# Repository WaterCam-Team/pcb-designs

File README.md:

# SU WaterCam PCB

Custom KiCad HAT for the **SU-WaterCam** project. Stacks on a Raspberry Pi 4B via a WittyPi 4 RTC/power-manager board, adding thermal imaging, LoRaWAN telemetry, IMU orientation, and environmental sensing.

**Software repo:** [mandeeps/SU-WaterCam](https://github.com/mandeeps/SU-WaterCam)  
**Schematic/pin map:** [PIN_MAP.md](PIN_MAP.md)

---

## Stack Order

Raspberry Pi 4B → WittyPi 4 (stacking header) → WaterCam HAT

---

## Components

| Reference | Part | Interface | Notes |
|-----------|------|-----------|-------|
| U2 | Adafruit BNO055 STEMMA QT | I2C1 (0x28) | 9-DOF IMU; INT→GPIO20, RST→GPIO16 |
| U3 | Multitech MTDOT-915 | UART5 (GPIO12/13) | LoRaWAN; always-on 3.3 V from WittyPi J3 |
| U1 | Adafruit AHT20 | I2C1 (0x38) | Temp/humidity |
| J2 | FLIR Lepton Breakout v2 | SPI0 + I2C1 | 2×10 header; SPI for image data, I2C for CCI |
| J3 | WittyPi 4 P3 header | — | Taps always-on 3.3 V and SW pin for mDot |
| Q1 | MOSFET | — | mDot PB_1 pulls WittyPi SW low for remote wake |

---

## Power Domains

| Rail | Source | Powers |
|------|--------|--------|
| +3V3 (Pi) | Pi J1 pin 1 | AHT20, BNO055 breakout, I2C pull-ups R6/R7 |
| 5 V (Pi) | Pi J1 pin 2/4 | FLIR Lepton VIN (J2-P2) |
| 3.3 V (always-on) | WittyPi J3 pin 2 | mDot VDD, mDot NRESET pull-up — survives Pi shutdown |

---

## PCB Details

- **Layers:** 2 (F.Cu, B.Cu)
- **Signal traces:** 0.25 mm
- **Power traces:** 0.5 mm
- **Clearance:** 0.20 mm (default net class)

---

## PCB Images

- **Wiring/Layout Diagram**  

- **PCB Render**

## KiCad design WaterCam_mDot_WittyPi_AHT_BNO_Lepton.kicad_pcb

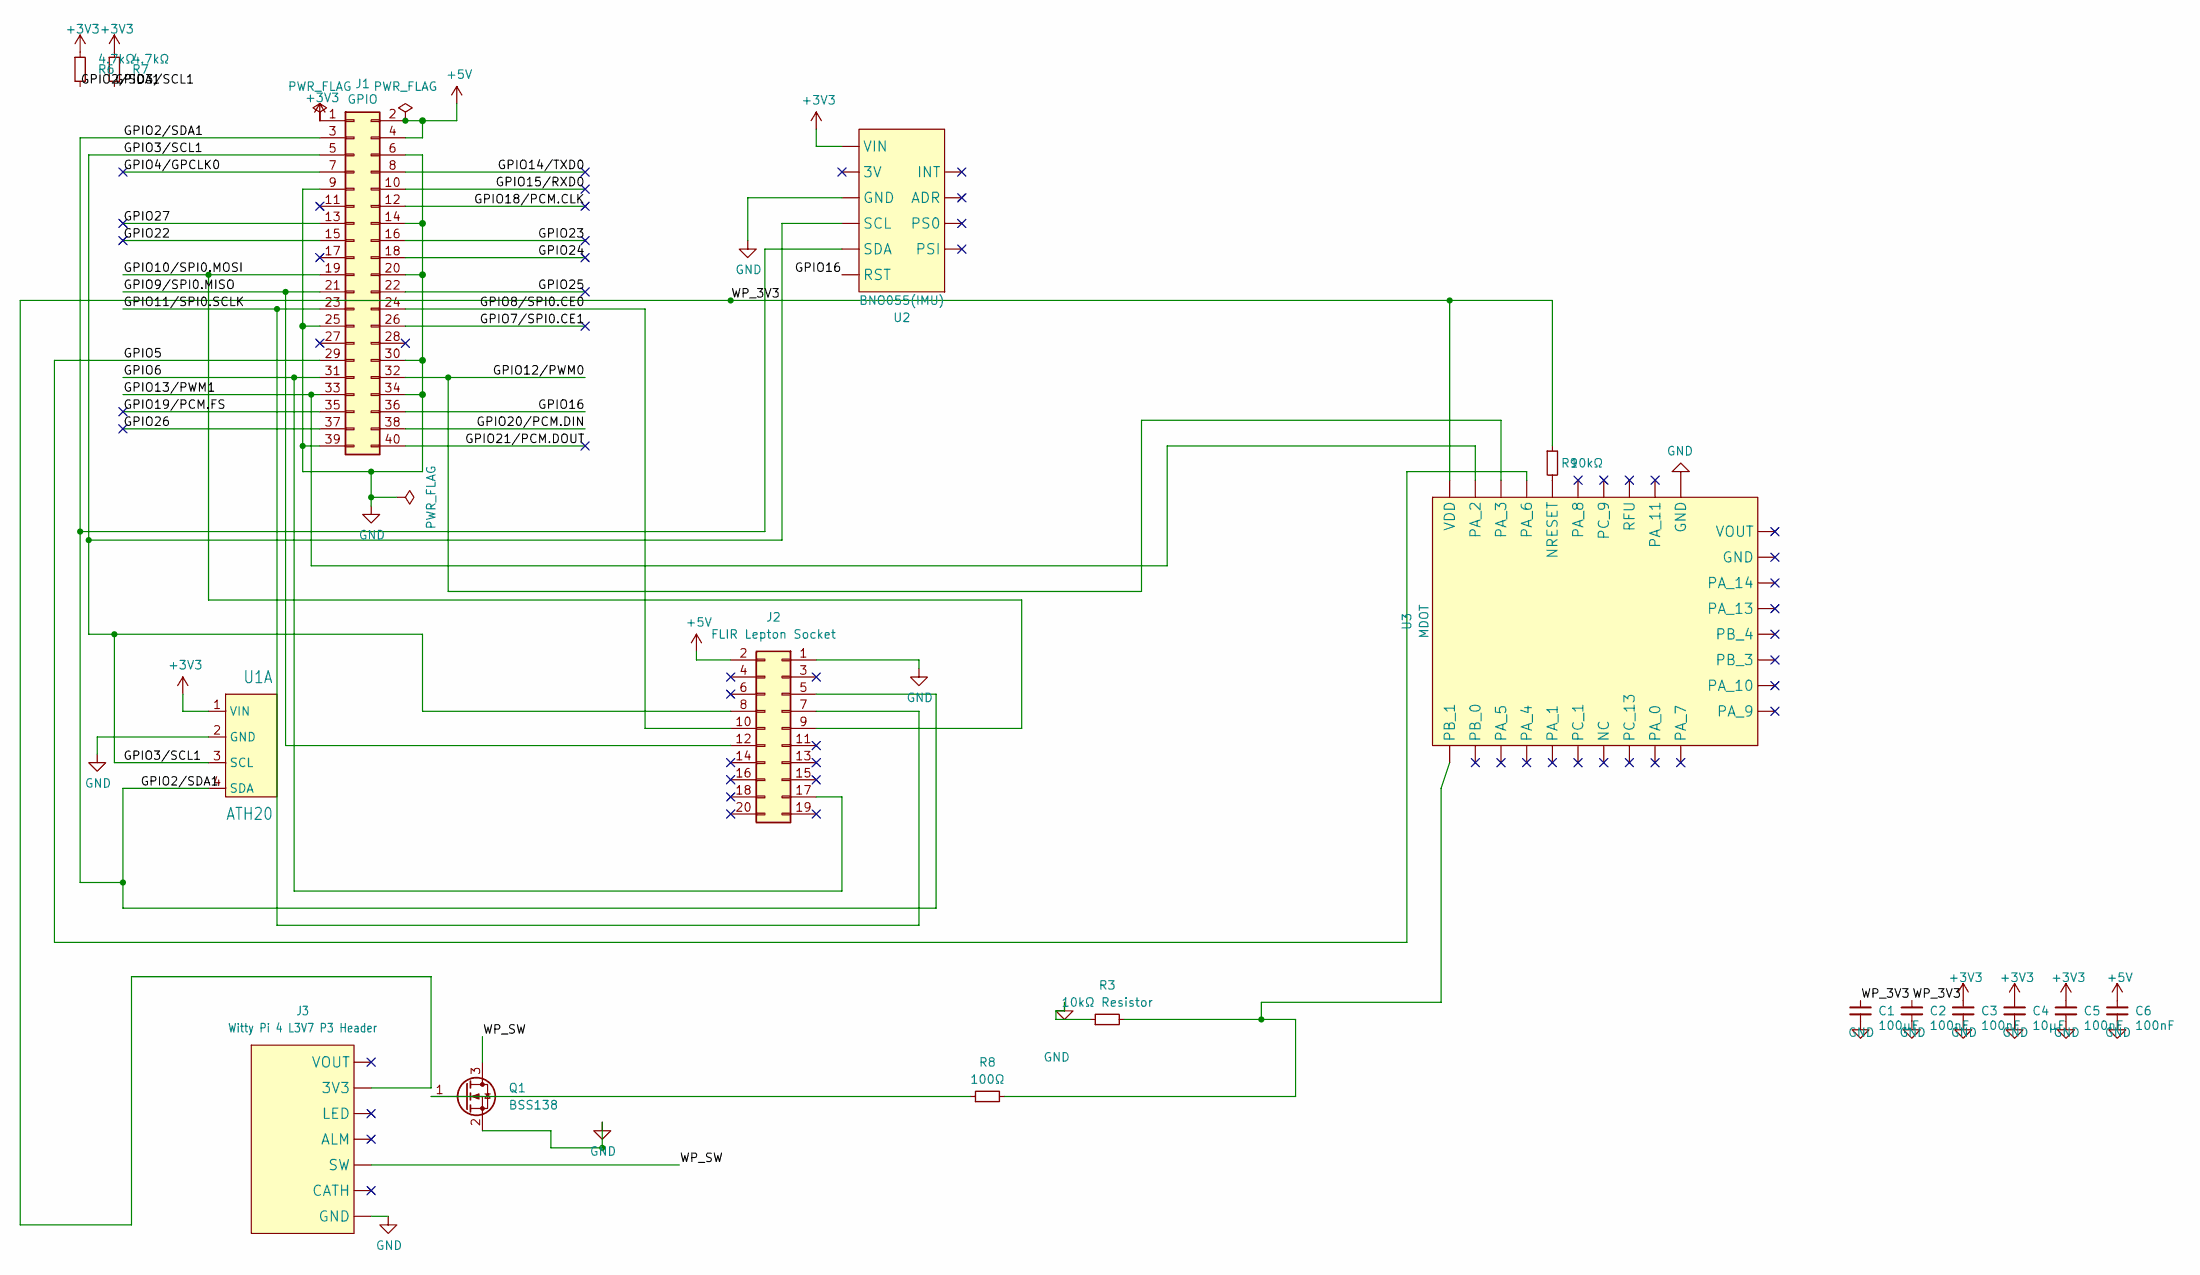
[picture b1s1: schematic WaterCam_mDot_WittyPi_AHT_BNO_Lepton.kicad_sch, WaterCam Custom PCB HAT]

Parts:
C1: 100µF; C_0805_2012Metric
C2, C3, C5, C6: 100nF; C_0402_1005Metric
C4: 10µF; C_0402_1005Metric
J1: GPIO; MODULE_RASPBERRY_PI_4B_4GB
J2: FLIR Lepton Socket; FLIR Lepton Breakout Board (Vertical)
J3: Witty Pi 4 L3V7 P3 Header; WittyPi4_Simple
Q1: BSS138; SOT-23
R3: 10kΩ Resistor; R_Axial_DIN0207_L6.3mm_D2.5mm_P2.54mm_Vertical
R6, R7: 4.7kΩ; R_0402_1005Metric
R8: 100Ω; R_0402_1005Metric
R9: 10kΩ; R_0402_1005Metric
U1: ATH20; AHT20 Breakout Board
U2: BNO055(IMU); BNO-055 Breakout
U3: MDOT; MTDOT

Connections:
+3V3: C3.1, C4.1, C5.1, J1.1, R6.1, R7.1, U1.1 (VIN), U2.6 (VIN)
+5V: C6.1, J1.2, J1.4, J2.2
/GPIO2/SDA1: J1.3, J2.5, R6.2, U1.4 (SDA), U2.2 (SDA)
/GPIO3/SCL1: J1.5, J2.8, R7.2, U1.3 (SCL), U2.3 (SCL)
/GPIO4/GPCLK0: J1.7
/GPIO5: J1.29, U3.4 (PA_6)
/GPIO6: J1.31, J2.17
/GPIO7/SPI0.CE1: J1.26
/GPIO8/SPI0.CE0: J1.24, J2.10
/GPIO9/SPI0.MISO: J1.21, J2.12
/GPIO10/SPI0.MOSI: J1.19, J2.9
/GPIO11/SPI0.SCLK: J1.23, J2.7
/GPIO12/PWM0: J1.32, U3.3 (PA_3)
/GPIO13/PWM1: J1.33, U3.2 (PA_2)
/GPIO14/TXD0: J1.8
/GPIO15/RXD0: J1.10
/GPIO16: J1.36, U2.1 (RST)
/GPIO18/PCM.CLK: J1.12
/GPIO19/PCM.FS: J1.35
/GPIO20/PCM.DIN: J1.38
/GPIO21/PCM.DOUT: J1.40
/GPIO22: J1.15
/GPIO23: J1.16
/GPIO24: J1.18
/GPIO25: J1.22
/GPIO26: J1.37
/GPIO27: J1.13
/WP_3V3: C1.1, C2.1, J3.2 (3V3), R9.1, U3.1 (VDD)
/WP_SW: J3.5 (SW), Q1.3 (D)
GND: C1.2, C2.2, C3.2, C4.2, C5.2, C6.2, J1.6, J1.9, J1.14, J1.20, J1.25, J1.30, J1.34, J1.39, J2.1, J3.7 (GND), Q1.2 (S), R3.1, U1.2 (GND), U2.4 (GND), U3.10 (GND)
unnamed: Q1.1 (G), R8.1
unnamed: R9.2, U3.5 (NRESET)
unnamed: R3.2, R8.2, U3.19 (PB_1)

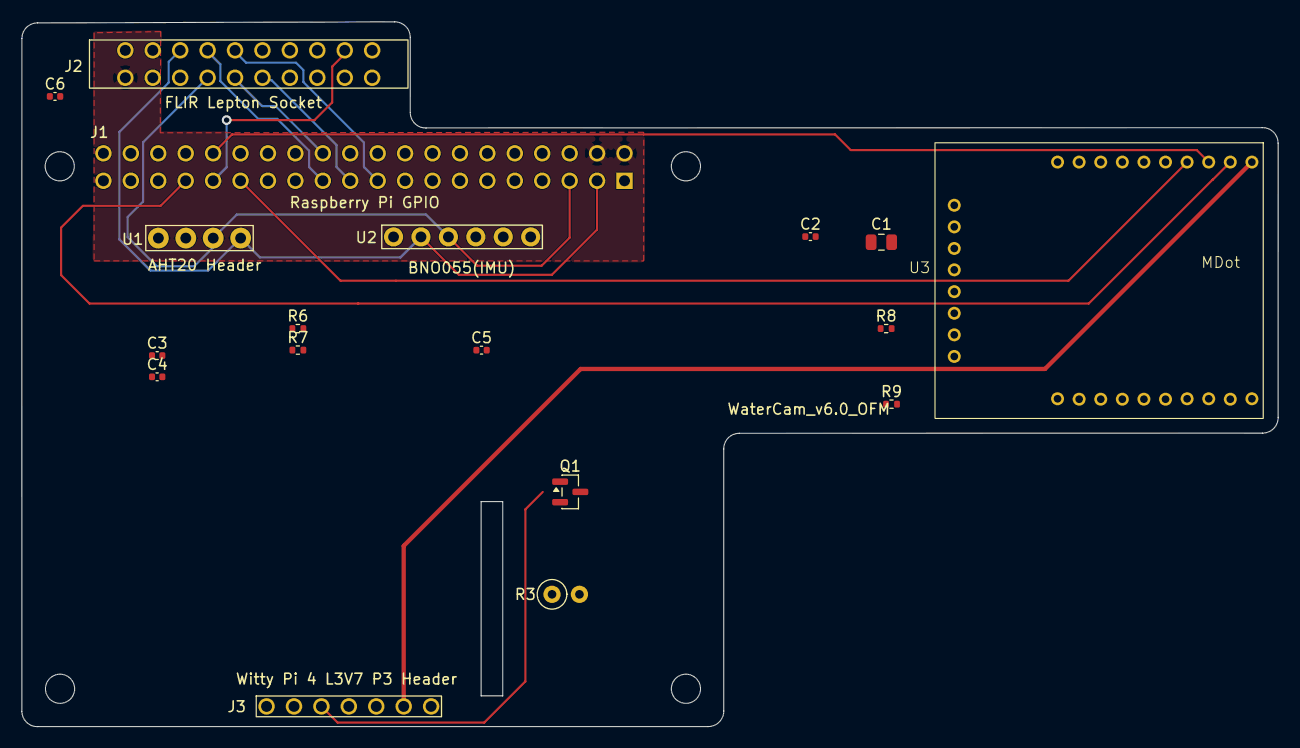
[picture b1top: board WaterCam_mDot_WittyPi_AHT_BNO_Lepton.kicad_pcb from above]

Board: 2 copper layers, 116.3 x 65.3 mm, 18 parts (1 on the bottom side), 19 nets.

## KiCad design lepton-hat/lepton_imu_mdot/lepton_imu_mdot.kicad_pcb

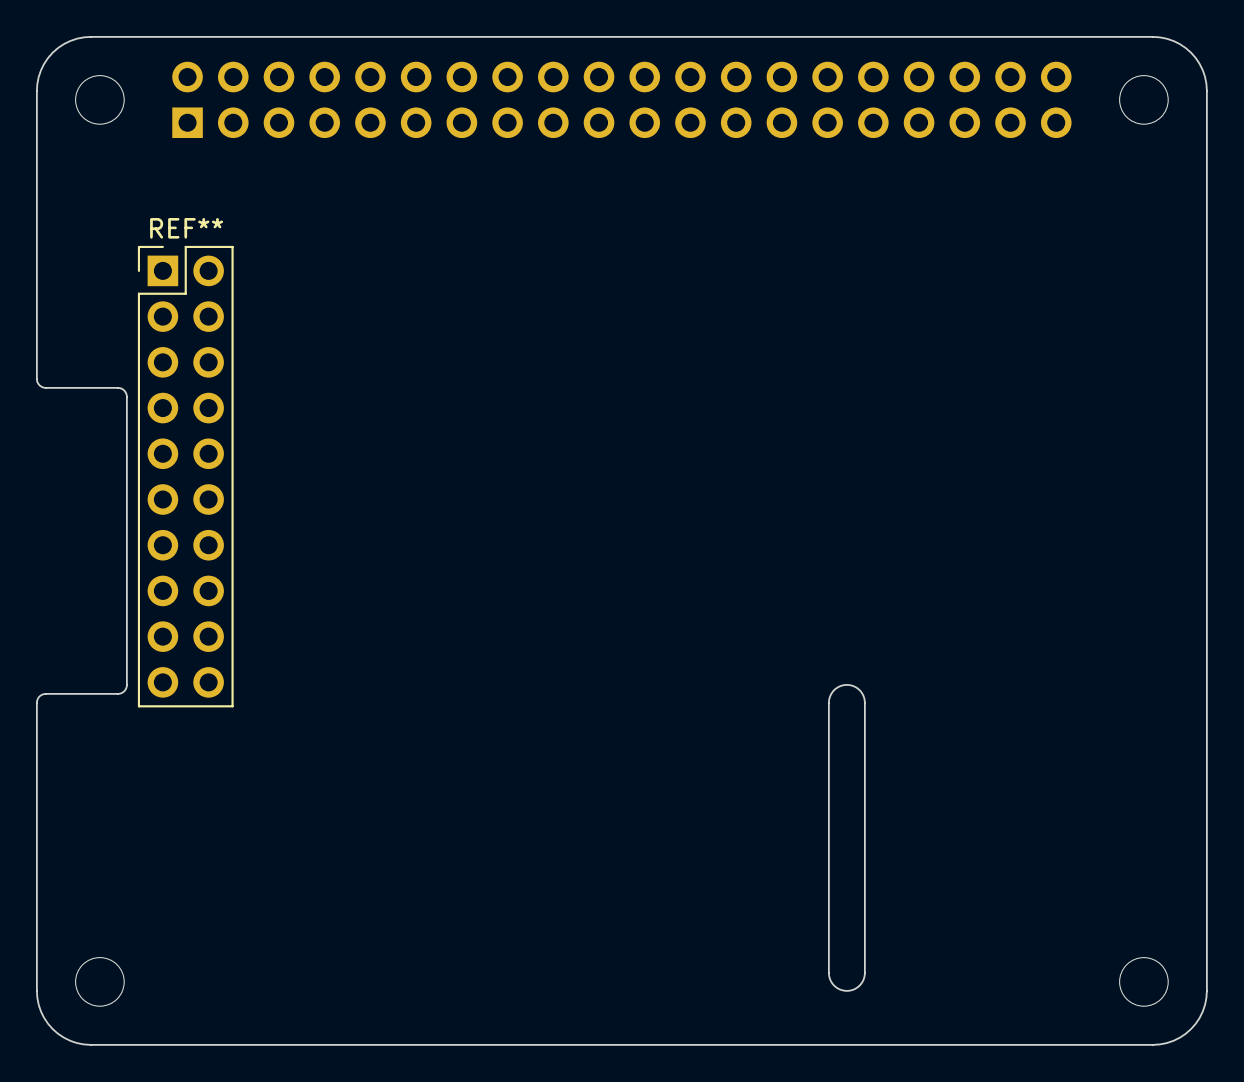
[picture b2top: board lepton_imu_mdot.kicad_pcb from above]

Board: 2 copper layers, 65.0 x 56.0 mm, 5 parts (1 on the bottom side), 3 nets, no tracks yet.

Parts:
J1: GPIO; PinSocket_2x20_P2.54mm_Vertical
MH1, MH2, MH3, MH4: MountingHole_2.7mm_M2.5

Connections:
+3V3: J1.1, J1.17
+5V: J1.2, J1.4
GND: J1.6, J1.9, J1.14, J1.20, J1.25, J1.30, J1.34, J1.39

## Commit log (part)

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2026-04-18 documentation updates
